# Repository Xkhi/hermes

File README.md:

# Project Hermes 

Property of [Waseda University](https://www.waseda.jp/top/en) [Graduate School of Creative Science and Engineering](http://www.cse.sci.waseda.ac.jp/en/).
Developed by [Javier Alvarez](mailto:javier.alvarez@akane.waseda.jp).

Project Hermes is a communication hub for sensors, developed specifically for WU's Sensor Team in Sugano Lab. 

## Status
- [x] Requirements definition
- [x] Conceptual design
- [x] Schematics
- [x] PCB
- [ ] Manufacture
- [ ] Programming

### Status Overview
The project has finished establishing requirements, concepts and schematics, and the PCB layout design has finished. The manufacturing process will begin soon.

## Specifications
The aim for the device are listed as follows:

* Act as a communication HUB for 5 sensors (I<sup>2</sup>C)
* Provide a network for communication between devices by a common bus (I<sup>2</sup>C)
* Power input 5V~12V

## Contact

For questions regarding the device:

* Design: [Javier Alvarez](mailto:javier.alvarez@akane.waseda.jp)
* Ownership: [Alexander Schmitz](mailto:schmitz.alexander@gmail.com), [Tito Tomo](mailto:tito@toki.waseda.jp), [Sophon Somlor](mailto:sophon@sugano.mech.waseda.ac.jp)

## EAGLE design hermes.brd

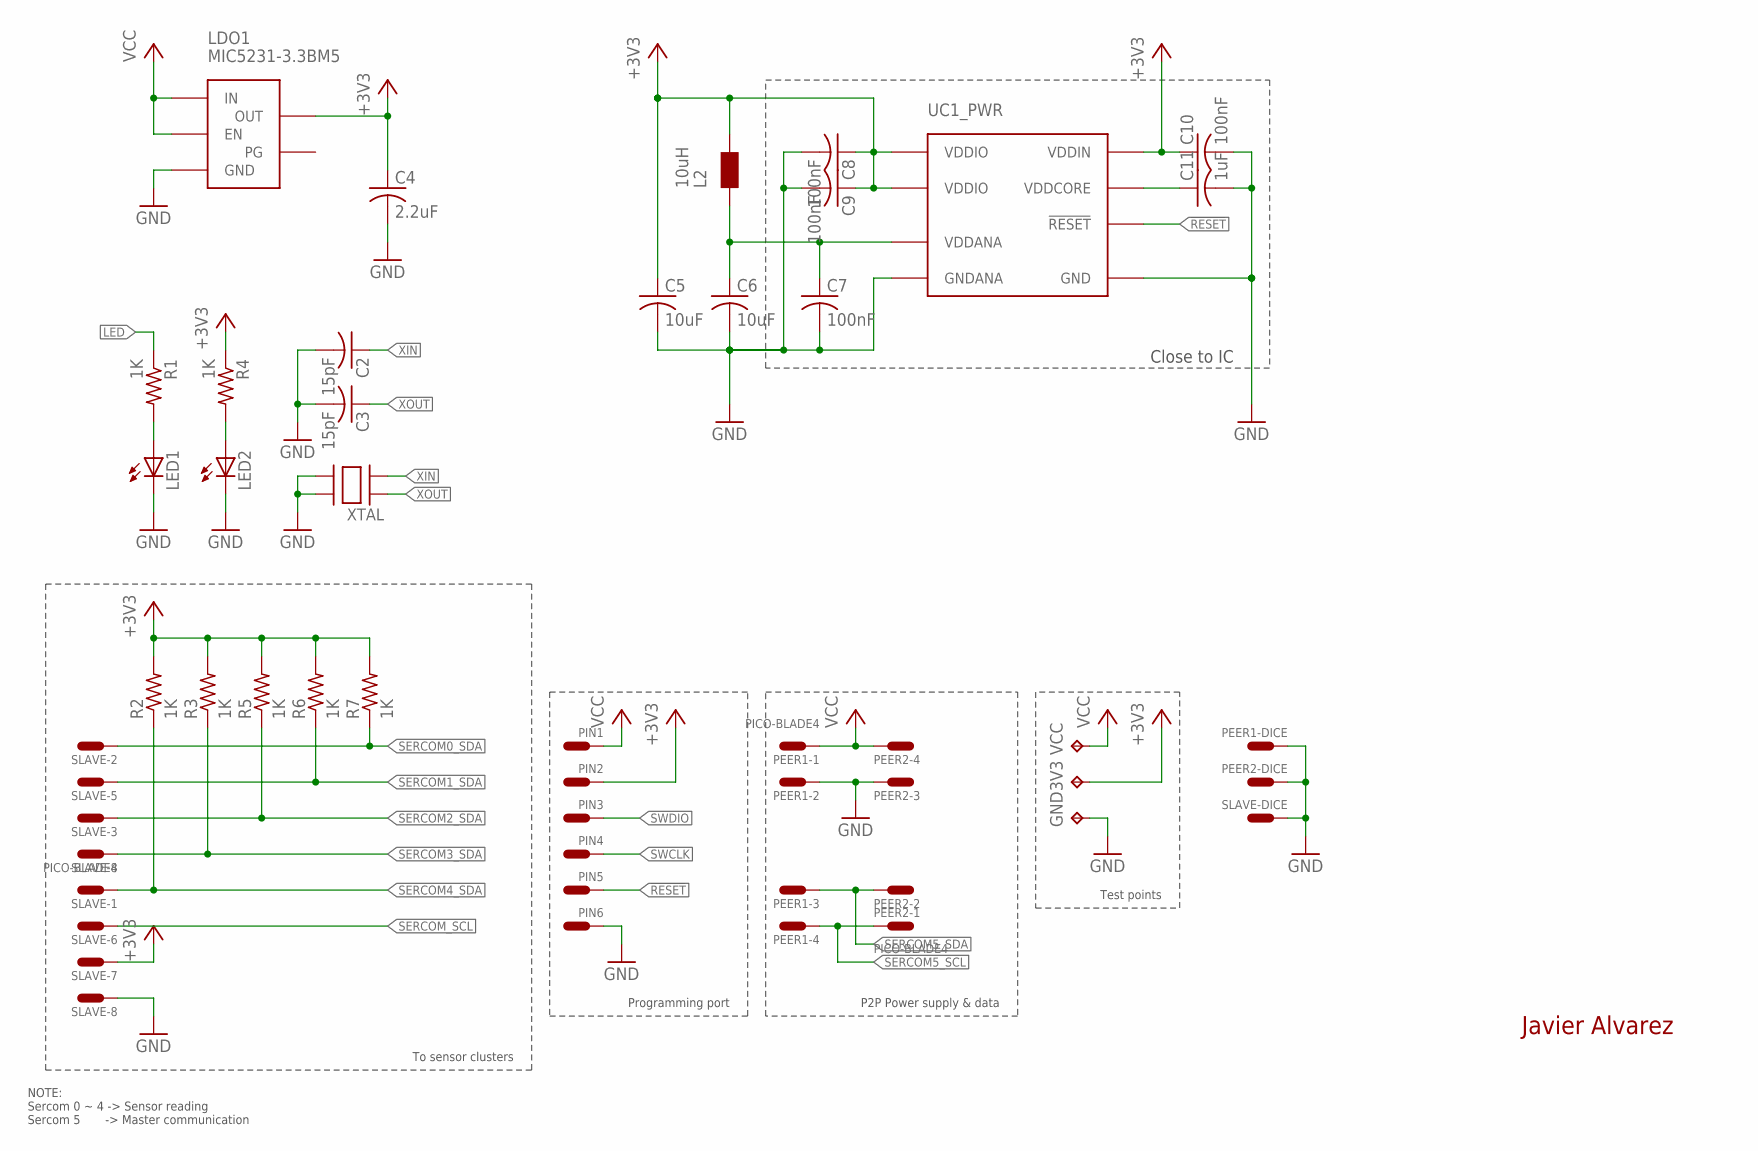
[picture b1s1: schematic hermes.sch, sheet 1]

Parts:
3V3: TPB1,27; B1,27
C2, C3: 15pF; C0201
C4: 2.2uF; C0201
C5, C6: 10uF; C0402
C7, C8, C9, C10: 100nF; C0201
C11: 1uF; C0201
GND: TPB1,27; B1,27
L2: 10uH; L2215
LDO1: MIC5231-3.3BM5; SOT-23-5
LED1, LED2: LED_ESML0603; LED_SML0603
PEER1, PEER2: PICO-BLADE4
PIN1, PIN2, PIN3, PIN4, PIN5, PIN6: SINGLE-PIN; PAD5025
R1, R2, R3, R4, R5, R6, R7: 1K; R0201
SLAVE: PICO-BLADE8
UC1: ATSAMD20G-QFN48; QFN-48
VCC: TPB1,27; B1,27
XTAL: LFXTAL059596CUTT; 2X1.6

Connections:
!RESET: PIN5.P$1, UC1.P$40 (!RESET)
+3V3: 3V3.TP, C4.1, C5.1, C8.1, C9.1, C10.1, L2.P$2, LDO1.P$4 (OUT), PIN2.P$1, R2.2, R3.2, R4.1, R5.2, R6.2, R7.2, SLAVE.P$9, UC1.P$17 (VDDIO), UC1.P$36 (VDDIO), UC1.P$44 (VDDIN)
GND: C2.2, C3.2, C4.2, C5.2, C6.2, C7.2, C8.2, C9.2, C10.2, C11.2, GND.TP, LDO1.P$2 (GND), LED1.C, LED2.C, PEER1.P$1, PEER1.P$2, PEER1.P$4, PEER2.P$1, PEER2.P$2, PEER2.P$5, PIN6.P$1, SLAVE.P$1, SLAVE.P$2, SLAVE.P$10, UC1.P$5 (GNDANA), UC1.P$18 (GND), UC1.P$35 (GND), UC1.P$42 (GND), UC1.P$49 (GND), XTAL.GND@1 (GND), XTAL.GND@2 (GND)
LED: R1.1; also elsewhere on the board
unnamed: C6.1, C7.1, L2.P$1, UC1.P$6 (VDDANA)
unnamed: C11.1, UC1.P$43 (VDDCORE)
unnamed: LED1.A, R1.2
unnamed: LED2.A, R4.2
SERCOM0_SDA: R7.1, SLAVE.P$4; also elsewhere on the board
SERCOM1_SDA: R6.1, SLAVE.P$7; also elsewhere on the board
SERCOM2_SDA: R5.1, SLAVE.P$5; also elsewhere on the board
SERCOM3_SDA: R3.1, SLAVE.P$6; also elsewhere on the board
SERCOM4_SDA: R2.1, SLAVE.P$3; also elsewhere on the board
SERCOM5_SCL: PEER1.P$6, PEER2.P$3; also elsewhere on the board
SERCOM5_SDA: PEER1.P$5, PEER2.P$4; also elsewhere on the board
SERCOM_SCL: SLAVE.P$8; also elsewhere on the board
SWCLK: PIN4.P$1; also elsewhere on the board
SWDIO: PIN3.P$1; also elsewhere on the board
VCC: LDO1.P$1 (EN), LDO1.P$3 (IN), PEER1.P$3, PEER2.P$6, PIN1.P$1, VCC.TP
XIN: C2.1, XTAL.XTAL@1 (XTAL); also elsewhere on the board
XOUT: C3.1, XTAL.XTAL@2 (XTAL); also elsewhere on the board

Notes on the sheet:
Close to IC
Javier Alvarez
NOTE: Sercom 0 ~ 4 -> Sensor reading Sercom 5 -> Master communication
To sensor clusters
Programming port
P2P Power supply & data
Test points

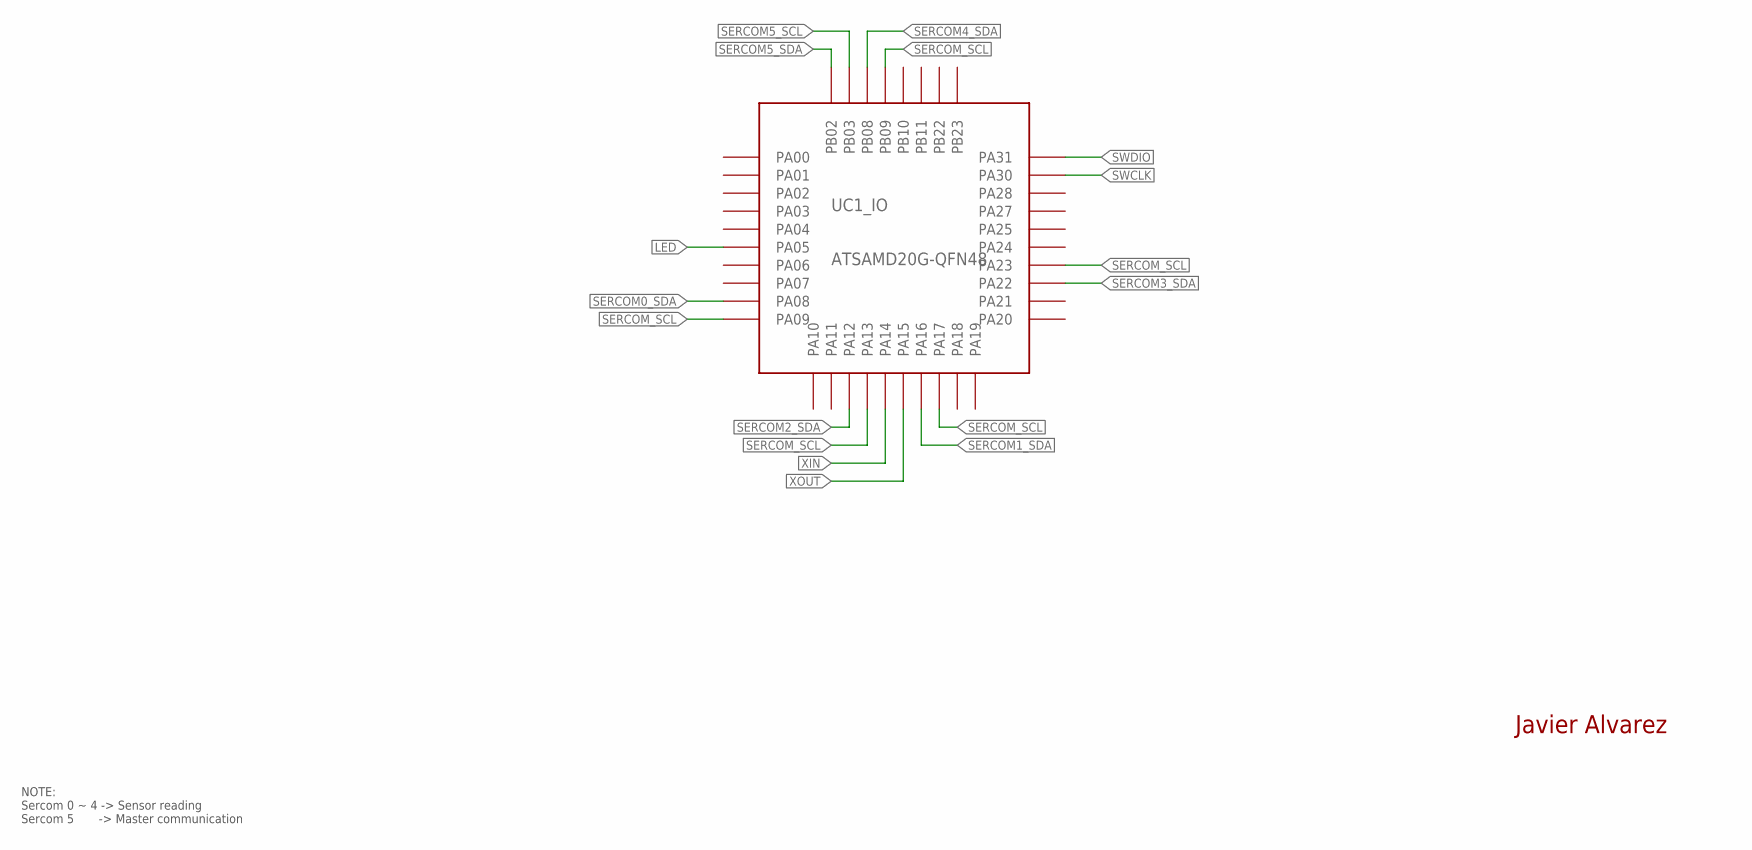
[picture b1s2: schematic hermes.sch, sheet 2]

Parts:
UC1: ATSAMD20G-QFN48; QFN-48

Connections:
LED: UC1.P$10 (PA05); also elsewhere on the board
SERCOM0_SDA: UC1.P$13 (PA08); also elsewhere on the board
SERCOM1_SDA: UC1.P$25 (PA16); also elsewhere on the board
SERCOM2_SDA: UC1.P$21 (PA12); also elsewhere on the board
SERCOM3_SDA: UC1.P$31 (PA22); also elsewhere on the board
SERCOM4_SDA: UC1.P$7 (PB08); also elsewhere on the board
SERCOM5_SCL: UC1.P$48 (PB03); also elsewhere on the board
SERCOM5_SDA: UC1.P$47 (PB02); also elsewhere on the board
SERCOM_SCL: UC1.P$8 (PB09), UC1.P$14 (PA09), UC1.P$22 (PA13), UC1.P$26 (PA17), UC1.P$32 (PA23); also elsewhere on the board
SWCLK: UC1.P$45 (PA30); also elsewhere on the board
SWDIO: UC1.P$46 (PA31); also elsewhere on the board
XIN: UC1.P$23 (PA14); also elsewhere on the board
XOUT: UC1.P$24 (PA15); also elsewhere on the board

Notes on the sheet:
Javier Alvarez
NOTE: Sercom 0 ~ 4 -> Sensor reading Sercom 5 -> Master communication

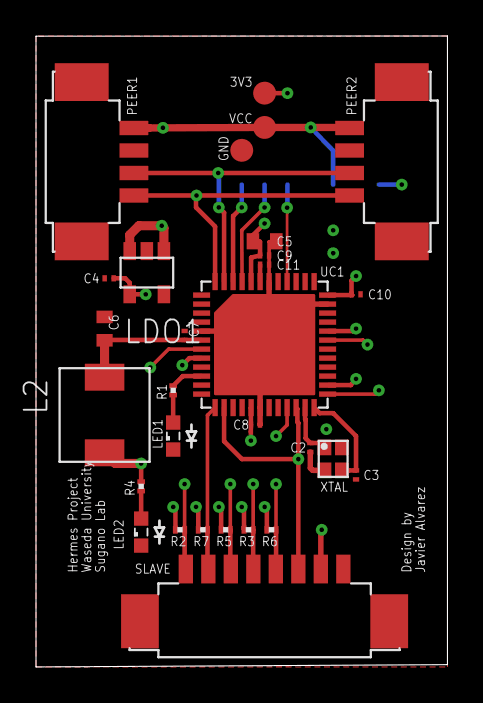
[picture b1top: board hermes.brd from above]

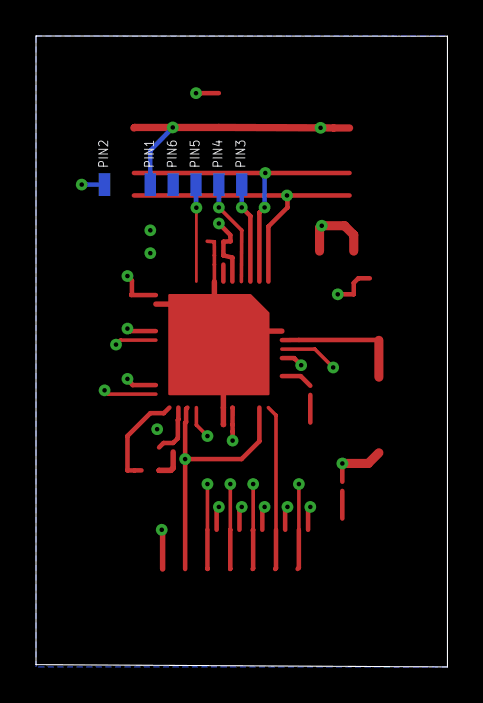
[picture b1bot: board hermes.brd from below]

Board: 4 copper layers, 22.9 x 35.1 mm, 35 parts (6 on the bottom side), 21 nets.

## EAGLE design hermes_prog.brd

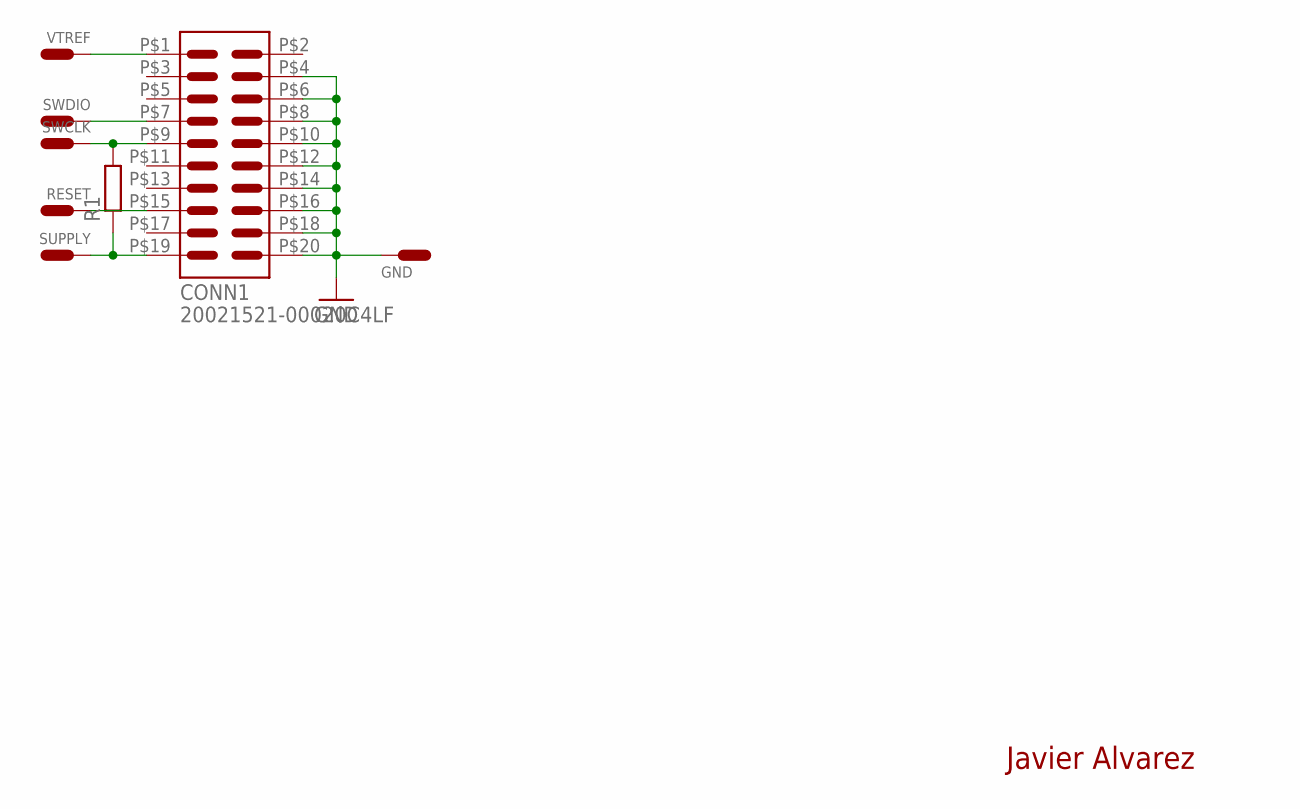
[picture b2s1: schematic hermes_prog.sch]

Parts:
CONN1: 20021521-00020C4LF; JTAG-20
GND: S7231-45R; SPRING-CONTACT
R1: R-EU_0204/2V; 0204V
RESET: S7231-45R; SPRING-CONTACT
SUPPLY: S7231-45R; SPRING-CONTACT
SWCLK: S7231-45R; SPRING-CONTACT
SWDIO: S7231-45R; SPRING-CONTACT
VTREF: S7231-45R; SPRING-CONTACT

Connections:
GND: CONN1.P$4, CONN1.P$6, CONN1.P$8, CONN1.P$10, CONN1.P$12, CONN1.P$14, CONN1.P$16, CONN1.P$18, CONN1.P$20, GND.P$1, GND.P$2
RESET: CONN1.P$15, RESET.P$1, RESET.P$2
SUPPLY: CONN1.P$19, R1.1, SUPPLY.P$1, SUPPLY.P$2
SWCLK: CONN1.P$9, R1.2, SWCLK.P$1, SWCLK.P$2
SWDIO: CONN1.P$7, SWDIO.P$1, SWDIO.P$2
VTREF: CONN1.P$1, VTREF.P$1, VTREF.P$2

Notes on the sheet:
Javier Alvarez

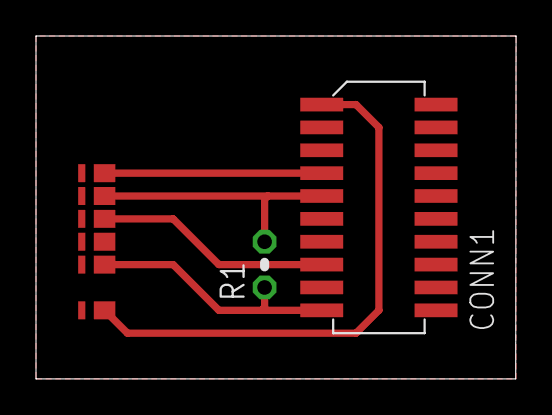
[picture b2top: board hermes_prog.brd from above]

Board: 2 copper layers, 26.7 x 19.1 mm, 8 parts (0 on the bottom side), 6 nets.

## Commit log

2017-12-15 Initial commit, shcematics only
2017-12-17 -Add LDO -Add library -Notes to uC PWR
2017-12-21 -SCH: Add placeholders for XTAL and LED -LBR: Add symbolic connection
2017-12-23 -Add I2C placeholders
2017-12-23 -Add README.md
2017-12-30 - Correct README file - Remove tracking from eagle.epf - Add .gitignore configuration file
2018-01-06 -Add XTAL to library -Add LDO to library -Add XTAL and LDO to schematics -Update .gitignore to ignore additional library files -Fix minor design flaws -Fix minor value errors in capacitance
2018-01-07 -Remove Reset switch -Add programming port -Correct minor connection issues
2018-01-14 -Correct README.md specifications -Add custom pads to library -Add programming connection to schematics
2018-01-21 -Confirm cabling -Add information
2018-01-21 -Update project status
2018-02-17 -Add correct connectors to library and board
2018-02-17 -Start layout board
2018-02-18 -Update Library -Correct P2P pins -Place general position of components
2018-03-11 -General routing
2018-03-25 MIniaturization of board process
2018-04-01 Reduction of board (Cont'd)
2018-04-14 First release of Hermes, Add Layout view and CAM files, Correct minor issues
2018-04-14 First release of Hermes, Add Layout view and CAM files, Add Bill of Materials (BOM), Correct minor issues
2018-04-14 Update README.md
    Updated the README file to update status
2018-05-13 Alternative version with LDO TS9013
2018-05-14 Updated CAM and BOM according to new parts used
2018-05-27 Add elements for programmer to library and programmer schematics
2018-06-03 Add programming board to design
2018-06-17 Replace components according to availability in digital stores (Capacitors and Inductors)
2018-06-17 -Update component description in library -Generate new BOM and CAM files from new configuration -Delete outdated layout and cam documents
2018-07-29 Updated the LEDs orientation
